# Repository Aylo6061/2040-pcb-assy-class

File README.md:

# 2040pad

An RP2040 macropad, and the board you build in my hands-on PCB soldering class.

## Features

- RP2040 microcontroller with USB-C
- 12 Choc key switches
- 12 SK6812MINI-E RGB LEDs
- PEC11R rotary encoder with push switch
- 128x32 SSD1306 OLED
- QMK firmware

## What's here

| Path | Contents |
|---|---|
| `2040pad/` | KiCad schematic and board, plus `gerbs.zip` |
| `firmware/qmk/2040pad/` | QMK keyboard definition, with build and flashing steps |
| `2040pad_assembly.html`, `2040pad_assembly.pdf` | Soldering and assembly guide |
| `docs/` | [Class web page](https://aylo6061.github.io/2040-pcb-assy-class/) |

The case design is coming soon.

## Status

The first board was built on 2026-11-05, and everything works.

## Credits and license

Based on the [Adafruit MacroPad RP2040](https://github.com/adafruit/Adafruit-MacroPad-RP2040-PCB),
designed by Limor Fried/Ladyada for Adafruit Industries. This is not an Adafruit
product, and Adafruit doesn't support or endorse it.

The hardware is released under Creative Commons Attribution-ShareAlike 3.0.
See [license.txt](license.txt).

The firmware is released under GPL-2.0-or-later. It is based on QMK's
`keyboards/adafruit/macropad` definition, Copyright 2022 Jose Pablo Ramirez.

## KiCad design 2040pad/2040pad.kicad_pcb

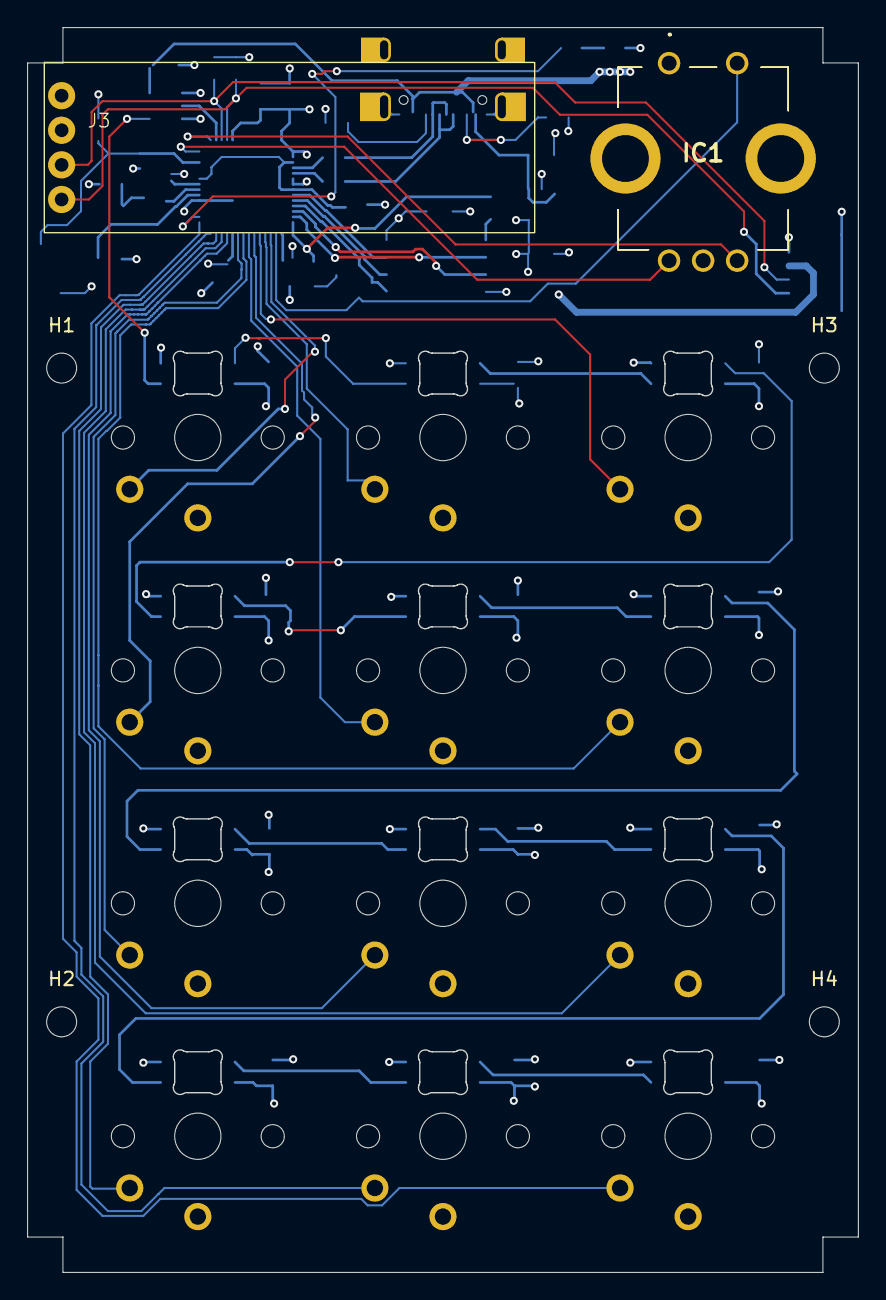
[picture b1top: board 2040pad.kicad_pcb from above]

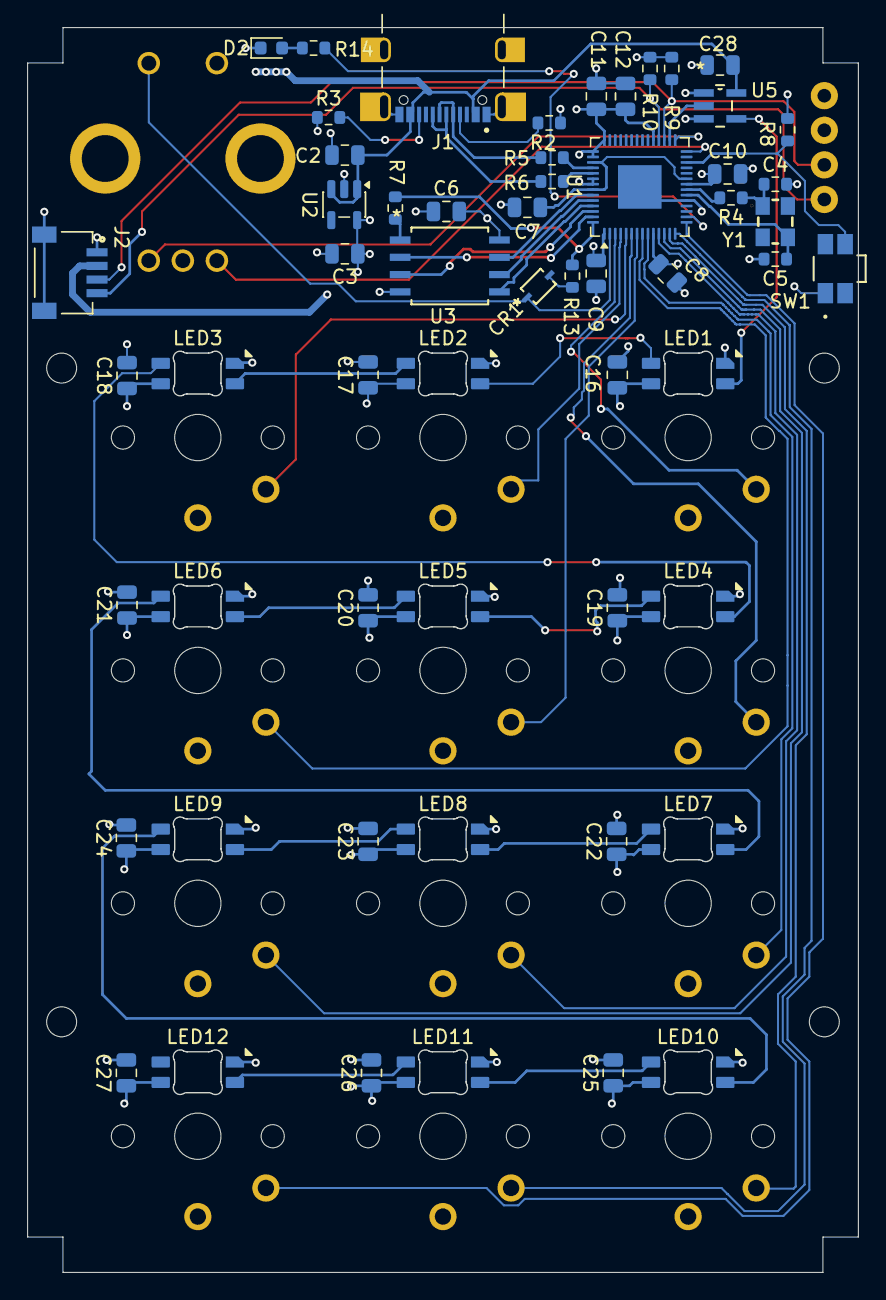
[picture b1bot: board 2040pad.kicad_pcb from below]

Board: 4 copper layers, 61.0 x 91.4 mm, 75 parts (57 on the bottom side), 54 nets.

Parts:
C2, C3: 10u; C_0805_2012Metric
C4, C5: 20p; R_0603_1608Metric
C6, C7, C8, C9, C10, C11, C12, C16, C17, C18, C19, C20, C21, C22, C23, C24, C25, C26, C27, C28: 1u; C_0805_2012Metric
CH1, CH2, CH3, CH4, CH5, CH6, CH7, CH8, CH9, CH10, CH11, CH12: choc_v1_SW_solder; SW_choc_v1_1u
CR1: 1N4148WS; SOD-323FL_ONS
D2: LED; LED_0603_1608Metric
H1, H2, H3, H4: MountingHole; MountingHole_2.2mm_M2
IC1: PEC11R-4230K-S0024; PEC11R4230KS0024
J1: UJ20-C-H-G-SMT-1-P16-TR; SAMESKY_UJ20-C-H-G-SMT-1-P16-TR
J2: SM04B-SRSS-TB_LF__SN_; JST_SM04B-SRSS-TB_LF__SN_
J3: Conn_01x04_Socket; Waveshare .91 oled
LED1, LED2, LED3, LED4, LED5, LED6, LED7, LED8, LED9, LED10, LED11, LED12: choc_SK6812MINI-E; LED_choc_6028R
R2, R3, R8, R9, R10, R14: 5k1; R_0603_1608Metric
R4, R13: 1k; R_0603_1608Metric
R5, R6: 22; R_0603_1608Metric
R7: 10k; R_0603_1608Metric
SW1: EVQ-P7J01P; SMD4_SW_EVQP7J_PAN
U1: RP2040; QFN-56-1EP_7x7mm_P0.4mm_EP3.2x3.2mm
U2: AP2112K-3.3; SOT-23-5
U3: W25Q64JVSSIM; SOIC_208MIL_WIN
U5: SN74AHCT1G125DBVR; DBV5
Y1: CX3225GB12000H0KPSC1; CX3225GB

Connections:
+1V2: C7.1, U1.23 (DVDD), U1.45 (VREG_VOUT), U1.50 (DVDD)
+3.3V: C3.1, C6.1, C8.1, C9.1, C10.1, C11.1, C12.1, J2.2, J3.1, R8.1, R9.1, R10.1, U1.1 (IOVDD), U1.10 (IOVDD), U1.22 (IOVDD), U1.33 (IOVDD), U1.42 (IOVDD), U1.43 (ADC_AVDD), U1.44 (VREG_VIN), U1.48 (USB_VDD), U1.49 (IOVDD), U2.5 (VOUT), U3.8 (VCC)
+5V: C2.1, C16.1, C17.1, C18.1, C19.1, C20.1, C21.1, C22.1, C23.1, C24.1, C25.1, C26.1, C27.1, C28.1, J1.A4_B9 (VBUS), J1.B4_A9 (VBUS__1), LED1.1 (VDD), LED2.1 (VDD), LED3.1 (VDD), LED4.1 (VDD), LED5.1 (VDD), LED6.1 (VDD), LED7.1 (VDD), LED8.1 (VDD), LED9.1 (VDD), LED10.1 (VDD), LED11.1 (VDD), LED12.1 (VDD), U2.1 (VIN), U2.3 (EN), U5.5 (VCC)
/SCL: J2.4, J3.4, R10.2, U1.32 (GPIO21)
/SDA: J2.3, J3.3, R9.2, U1.31 (GPIO20)
/keys+leds/Key1: CH1.1, U1.3 (GPIO1)
/keys+leds/Key2: CH2.1, U1.4 (GPIO2)
/keys+leds/Key3: CH3.1, U1.5 (GPIO3)
/keys+leds/Key4: CH4.1, U1.6 (GPIO4)
/keys+leds/Key5: CH5.1, U1.7 (GPIO5)
/keys+leds/Key6: CH6.1, U1.8 (GPIO6)
/keys+leds/Key7: CH7.1, U1.9 (GPIO7)
/keys+leds/Key8: CH8.1, U1.11 (GPIO8)
/keys+leds/Key9: CH9.1, U1.12 (GPIO9)
/keys+leds/Key10: CH10.1, U1.13 (GPIO10)
/keys+leds/Key11: CH11.1, U1.14 (GPIO11)
/keys+leds/Key12: CH12.1, U1.15 (GPIO12)
/keys+leds/Neopix_5v_in: LED1.3 (DIN), U5.4 (Y)
/keys+leds/Neopix_in: U1.30 (GPIO19), U5.2 (A)
/keys+leds/ROTA: IC1.A1 (A), U1.28 (GPIO17)
/keys+leds/ROTB: IC1.B1 (B), U1.29 (GPIO18)
/keys+leds/keyled1/led_out: LED2.2 (DOUT), LED3.3 (DIN)
/keys+leds/keyled2/led_out: LED3.2 (DOUT), LED4.3 (DIN)
/keys+leds/keyled3/led_out: LED4.2 (DOUT), LED5.3 (DIN)
/keys+leds/keyled4/led_out: LED5.2 (DOUT), LED6.3 (DIN)
/keys+leds/keyled5/led_out: LED6.2 (DOUT), LED7.3 (DIN)
/keys+leds/keyled6/led_out: LED7.2 (DOUT), LED8.3 (DIN)
/keys+leds/keyled7/led_out: LED8.2 (DOUT), LED9.3 (DIN)
/keys+leds/keyled8/led_out: LED9.2 (DOUT), LED10.3 (DIN)
/keys+leds/keyled10/led_in: LED10.2 (DOUT), LED11.3 (DIN)
/keys+leds/keyled10/led_out: LED11.2 (DOUT), LED12.3 (DIN)
/keys+leds/keyled/led_out: LED1.2 (DOUT), LED2.3 (DIN)
/micro+usb/D+: J1.A6 (DP1), J1.B6 (DP2), R6.1
/micro+usb/D-: J1.A7 (DN1), J1.B7 (DN2), R5.1
/micro+usb/QSPI_SCLK: U1.52 (QSPI_SCLK), U3.6 (CLK)
/micro+usb/QSPI_SD0: U1.53 (QSPI_SD0), U3.5 (DI(IO0))
/micro+usb/QSPI_SD1: U1.55 (QSPI_SD1), U3.2 (DO(IO1))
/micro+usb/QSPI_SD2: U1.54 (QSPI_SD2), U3.3 (nWP(IO2))
/micro+usb/QSPI_SD3: U1.51 (QSPI_SD3), U3.7 (nHOLD_nRESET)
/micro+usb/QSPI_SS: R7.1, R13.2, U1.56 (~QSPI_SS)
/micro+usb/USBBOOT: CR1.1, IC1.2 (NO), U1.2 (GPIO0)
/micro+usb/USERLED: R14.1, U1.16 (GPIO13)
/micro+usb/nRESET_2040: R8.2, SW1.3, U1.26 (RUN)
GND: C2.2, C3.2, C4.2, C5.2, C6.2, C7.2, C8.2, C9.2, C10.2, C11.2, C12.2, C16.2, C17.2, C18.2, C19.2, C20.2, C21.2, C22.2, C23.2, C24.2, C25.2, C26.2, C27.2, C28.2, CH1.2, CH2.2, CH3.2, CH4.2, CH5.2, CH6.2, CH7.2, CH8.2, CH9.2, CH10.2, CH11.2, CH12.2, D2.1 (K), IC1.1 (COM), IC1.C1 (C), IC1.MH1, IC1.MH2, J1.A1_B12 (GND), J1.B1_A12 (GND__1), J1.SH1 (SHIELD), J1.SH2 (SHIELD__1), J1.SH3 (SHIELD__2), J1.SH4 (SHIELD__3), J2.1, J2.S1 (SHIELD), J2.S2 (SHIELD__1), J3.2, LED1.4 (VSS), LED2.4 (VSS), LED3.4 (VSS), LED4.4 (VSS), LED5.4 (VSS), LED6.4 (VSS), LED7.4 (VSS), LED8.4 (VSS), LED9.4 (VSS), LED10.4 (VSS), LED11.4 (VSS), LED12.4 (VSS), R2.2, R3.2, SW1.1, U1.19 (TESTEN), U1.57 (GND), U2.2 (GND), U3.4 (GND), U5.1 (*OE), U5.3 (GND)
unnamed: C4.1, R4.1, Y1.1
unnamed: CR1.2, R13.1
unnamed: D2.2 (A), R14.2
unnamed: J1.A5 (CC1), R2.1
unnamed: J1.B5 (CC2), R3.1
unnamed: R5.2, U1.46 (USB_DM)
unnamed: R6.2, U1.47 (USB_DP)
unnamed: C5.1, U1.20 (XIN), Y1.3
unnamed: R4.2, U1.21 (XOUT)
unnamed: R7.2, U3.1 (nCS)
